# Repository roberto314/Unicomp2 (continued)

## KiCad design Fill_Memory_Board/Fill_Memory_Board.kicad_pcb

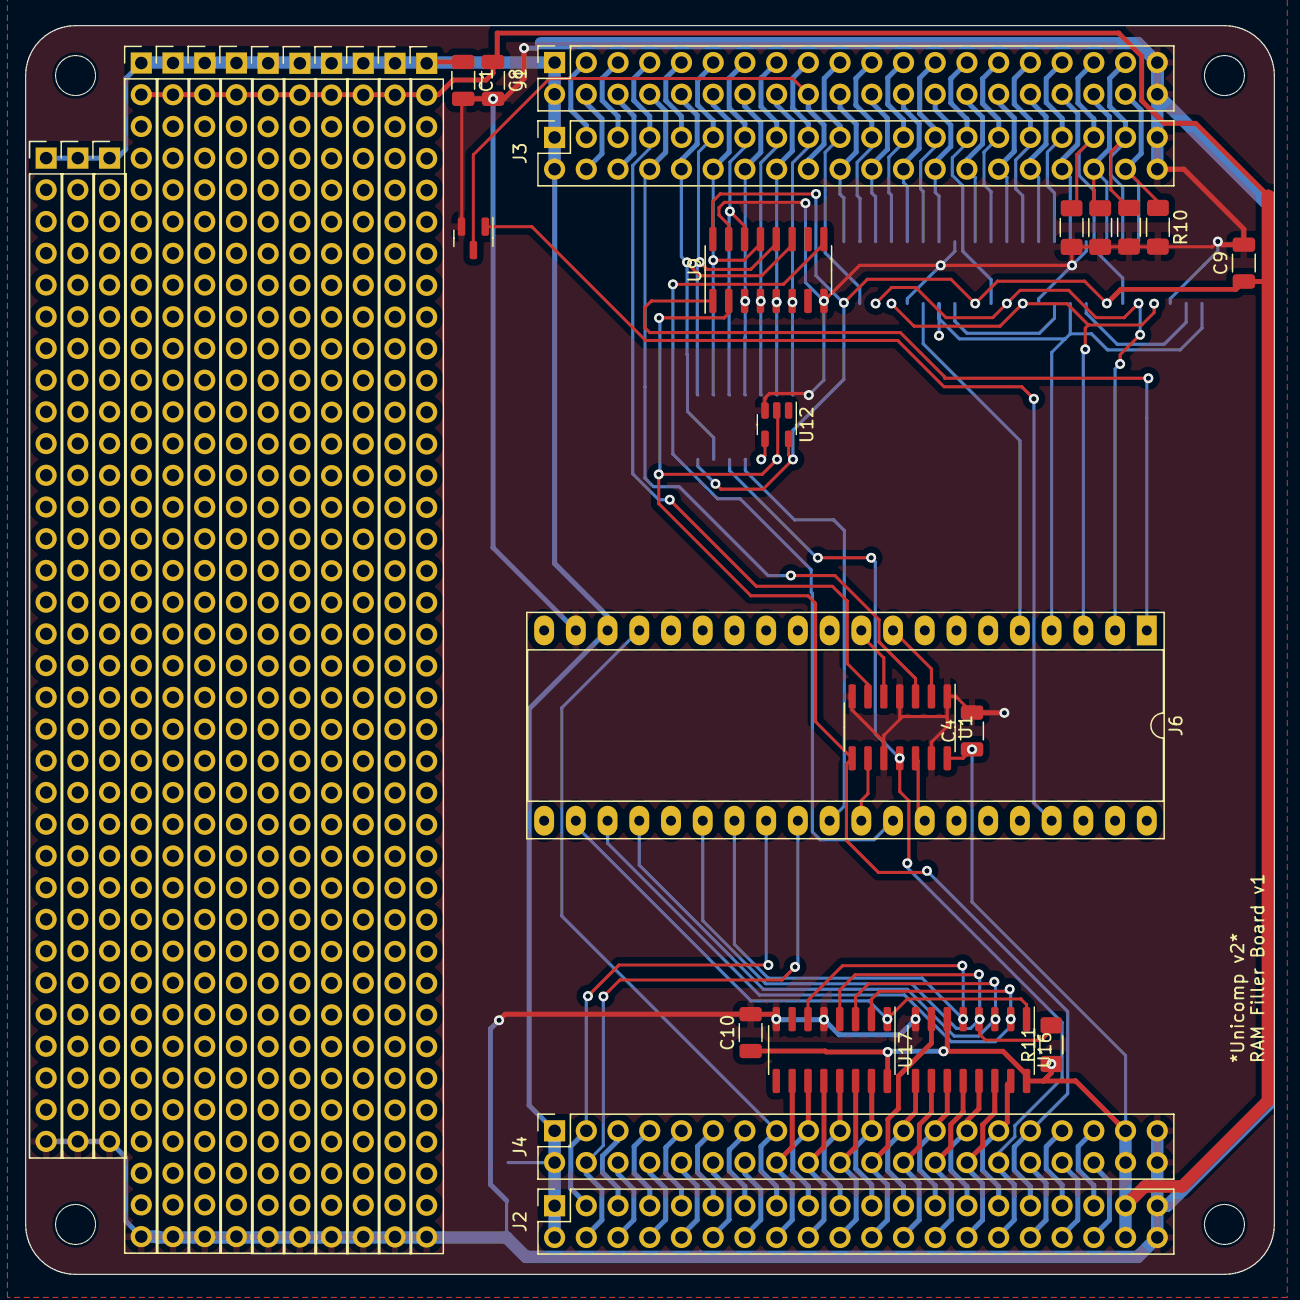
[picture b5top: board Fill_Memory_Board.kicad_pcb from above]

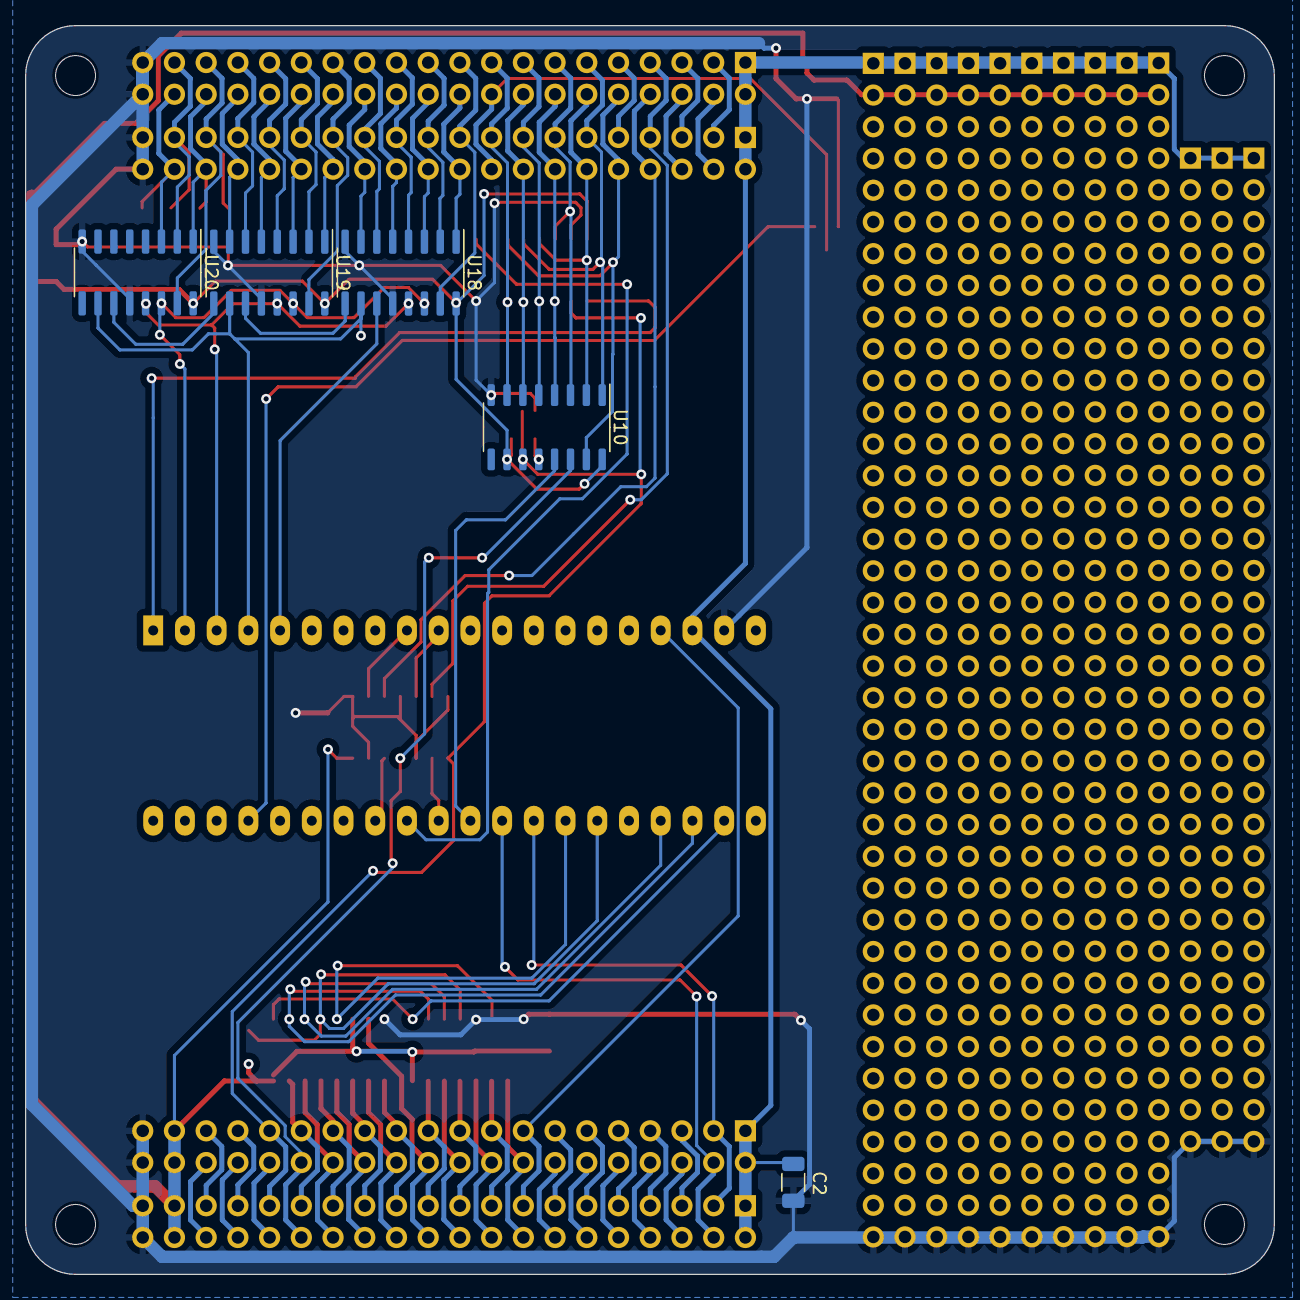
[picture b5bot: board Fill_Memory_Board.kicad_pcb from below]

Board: 2 copper layers, 100.0 x 100.0 mm, 43 parts (5 on the bottom side), 93 nets.

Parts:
C1, C2, C4, C8, C9, C10: 100n; C_1206_3216Metric
H1, H2, H3, H4: MountingHole; MountingHole_3.2mm_M3
J1, J2, J3, J4: BUS; PinSocket_2x20_P2.54mm_Vertical
J6: STM32F411; DIP-40_W15.24mm_Socket_LongPads
J20, J21, J32: Conn_01x32; PinHeader_1x32_P2.54mm_Vertical
J22, J23, J24, J25, J26, J27, J28, J29, J30, J31: Conn_01x38; PinHeader_1x38_P2.54mm_Vertical
Q1: PMV450ENEAR; SOT-23
R7, R8, R9, R10, R11: 10k; R_1206_3216Metric_Pad1.30x1.75mm_HandSolder
U1: 74LS125; SOIC-14_3.9x8.7mm_P1.27mm
U9: 74LS165; SOIC-16_3.9x9.9mm_P1.27mm
U10: 74LVC595; SO-16_3.9x9.9mm_P1.27mm
U12: 74AHC1G14; SOT-23-5
U16, U17: 74LVC138; SOIC-16_3.9x9.9mm_P1.27mm
U18, U19, U20: 74HC590; SOIC-16_3.9x9.9mm_P1.27mm

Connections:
+3V3: C4.1, C8.1, C9.1, C10.1, J2.37, J2.38, J4.37, J4.38, J22.2, J23.2, J24.2, J25.2, J26.2, J27.2, J28.2, J29.2, J30.2, J31.2, R11.1, U1.14 (VCC), U9.16 (VCC), U10.10 (~SRCLR), U10.16 (VCC), U12.5 (VCC), U16.6 (E3), U16.16 (VCC), U17.16 (VCC), U18.16 (VCC), U19.16 (VCC), U20.16 (VCC)
+5V: C1.1, C2.1, J1.1, J1.2, J2.1, J2.2, J3.1, J3.2, J4.1, J4.2, J6.18, J20.1, J21.1, J22.1, J23.1, J24.1, J25.1, J26.1, J27.1, J28.1, J29.1, J30.1, J31.1, J32.1
/A0: J1.19, J3.19, U18.15 (Q0)
/A1: J1.20, J3.20, U18.1 (Q1)
/A2: J1.21, J3.21, U18.2 (Q2)
/A3: J1.22, J3.22, U18.3 (Q3)
/A4: J1.23, J3.23, U18.4 (Q4)
/A5: J1.24, J3.24, U18.5 (Q5)
/A6: J1.25, J3.25, U18.6 (Q6)
/A7: J1.26, J3.26, U18.7 (Q7)
/A8: J1.27, J3.27, U19.15 (Q0)
/A9: J1.28, J3.28, U19.1 (Q1)
/A10: J1.29, J3.29, U19.2 (Q2)
/A11: J1.30, J3.30, U19.3 (Q3)
/A12: J1.31, J3.31, U19.4 (Q4)
/A13: J1.32, J3.32, U19.5 (Q5)
/A14: J1.33, J3.33, U19.6 (Q6)
/A15: J1.34, J3.34, U19.7 (Q7)
/A16: J1.35, J3.35, R7.1, U20.15 (Q0)
/A17: J1.36, J3.36, R8.1, U20.1 (Q1)
/A18: J1.37, J3.37, R9.1, U20.2 (Q2)
/A19: J1.38, J3.38, R10.1, U20.3 (Q3)
/B10: J6.37, Q1.1 (G)
/Bus/TDRTN: J2.32, J4.32
/CLKF: J2.14, J4.14
/CLKS: J2.13, J4.13
/CNT: J6.5, U18.11 (CPC)
/CPR: J6.3, U18.13 (CPR), U19.13 (CPR), U20.13 (CPR)
/D0: J1.10, J3.10, U9.11 (D0), U10.15 (QA)
/D1: J1.11, J3.11, U9.12 (D1), U10.1 (QB)
/D2: J1.12, J3.12, U9.13 (D2), U10.2 (QC)
/D3: J1.13, J3.13, U9.14 (D3), U10.3 (QD)
/D4: J1.14, J3.14, U9.3 (D4), U10.4 (QE)
/D5: J1.15, J3.15, U9.4 (D5), U10.5 (QF)
/D6: J1.16, J3.16, U9.5 (D6), U10.6 (QG)
/D7: J1.17, J3.17, U9.6 (D7), U10.7 (QH)
/MOSI: J2.30, J4.30, U1.11, U10.14 (SER)
/OFF/ON: J6.26, R11.2, U16.4 (E1), U17.4 (E1)
/PH0: J2.11, J4.11
/PHI1_e: J1.3, J3.3
/PHI2_e: J1.4, J3.4
/RES0: J2.7, J4.7
/RES1: J2.9, J4.9
/RX1: J2.10, J4.10
/RX2: J2.3, J4.3, J6.28
/RX3: J2.5, J4.5
/R/~W_e: J1.6, J3.6
/SCK: J2.31, J4.31, U1.8, U9.2 (CP), U10.11 (SRCLK), U12.2
/SEL0: J6.22, U16.1 (A0), U17.1 (A0)
/SEL1: J6.23, U16.2 (A1), U17.2 (A1)
/SEL2: J6.24, U16.3 (A2), U17.3 (A2)
/SEL4: J6.27, U16.5 (E2), U17.6 (E3)
/TCK: J2.35, J4.35
/TDI: J2.36, J4.36
/TDO: J2.34, J4.34
/TMS: J2.33, J4.33
/TX1: J2.8, J4.8
/TX2: J2.4, J4.4, J6.29
/TX3: J2.6, J4.6
/UMISO: J6.32, U9.9 (Q7)
/uMOSI: J6.33, U1.12
/uSCK: J6.31, U1.9
/~BUSFREE: J2.15, J4.15, J6.17
/~CNTOE: J6.2, U18.14 (~OE), U19.14 (~OE), U20.14 (~OE)
/~DATOE: J6.30, U10.13 (~OE)
/~IORD: J1.5, J3.5
/~IOWR: J1.9, J3.9
/~MRC: J6.4, U18.10 (~MRC), U19.10 (~MRC), U20.10 (~MRC)
/~MRD: J1.7, J3.7, U1.6
/~MWR: J1.8, J3.8, U1.3
/~PH0: J2.12, J4.12
/~PLD: J6.1, U9.1 (~PL)
/~RAMWE0: J2.29, J4.29, U16.15 (O0)
/~RAMWE1: J2.28, J4.28, U16.14 (O1)
/~RAMWE2: J2.27, J4.27, U16.13 (O2)
/~RAMWE3: J2.26, J4.26, U16.12 (O3)
/~RAMWE4: J2.25, J4.25, U16.11 (O4)
/~RAMWE5: J2.24, J4.24, U16.10 (O5)
/~RAMWE6: J2.23, J4.23, U16.9 (O6)
/~RAMWE7: J2.22, J4.22, U16.7 (O7)
/~RAMWE8: J2.21, J4.21, U17.15 (O0)
/~RAMWE9: J2.20, J4.20, U17.14 (O1)
/~RAMWE10: J2.19, J4.19, U17.13 (O2)
/~RAMWE11: J2.18, J4.18, U17.12 (O3)
/~RAMWE12: J2.17, J4.17, U17.11 (O4)
/~RAMWE13: J2.16, J4.16, U17.10 (O5)
/~RST: J1.18, J3.18, Q1.3 (D)
/~uMRD: J6.10, U1.5
/~uMWR: J6.9, U1.2
GND: C1.2, C2.2, C4.2, C8.2, C9.2, C10.2, J1.39, J1.40, J2.39, J2.40, J3.39, J3.40, J4.39, J4.40, J6.19, J20.32, J21.32, J22.38, J23.38, J24.38, J25.38, J26.38, J27.38, J28.38, J29.38, J30.38, J31.38, J32.32, Q1.2 (S), R7.2, R8.2, R9.2, R10.2, U1.1, U1.4, U1.7 (GND), U1.10, U1.13, U9.8 (GND), U9.15 (~CE), U10.8 (GND), U12.3 (GND), U16.8 (GND), U17.5 (E2), U17.8 (GND), U18.8 (GND), U18.12 (~CE), U19.8 (GND), U19.12 (~CE), U20.8 (GND), U20.12 (~CE)
unnamed: U10.12 (RCLK), U12.4
unnamed: U18.9 (~RCO), U19.11 (CPC)
unnamed: U19.9 (~RCO), U20.11 (CPC)

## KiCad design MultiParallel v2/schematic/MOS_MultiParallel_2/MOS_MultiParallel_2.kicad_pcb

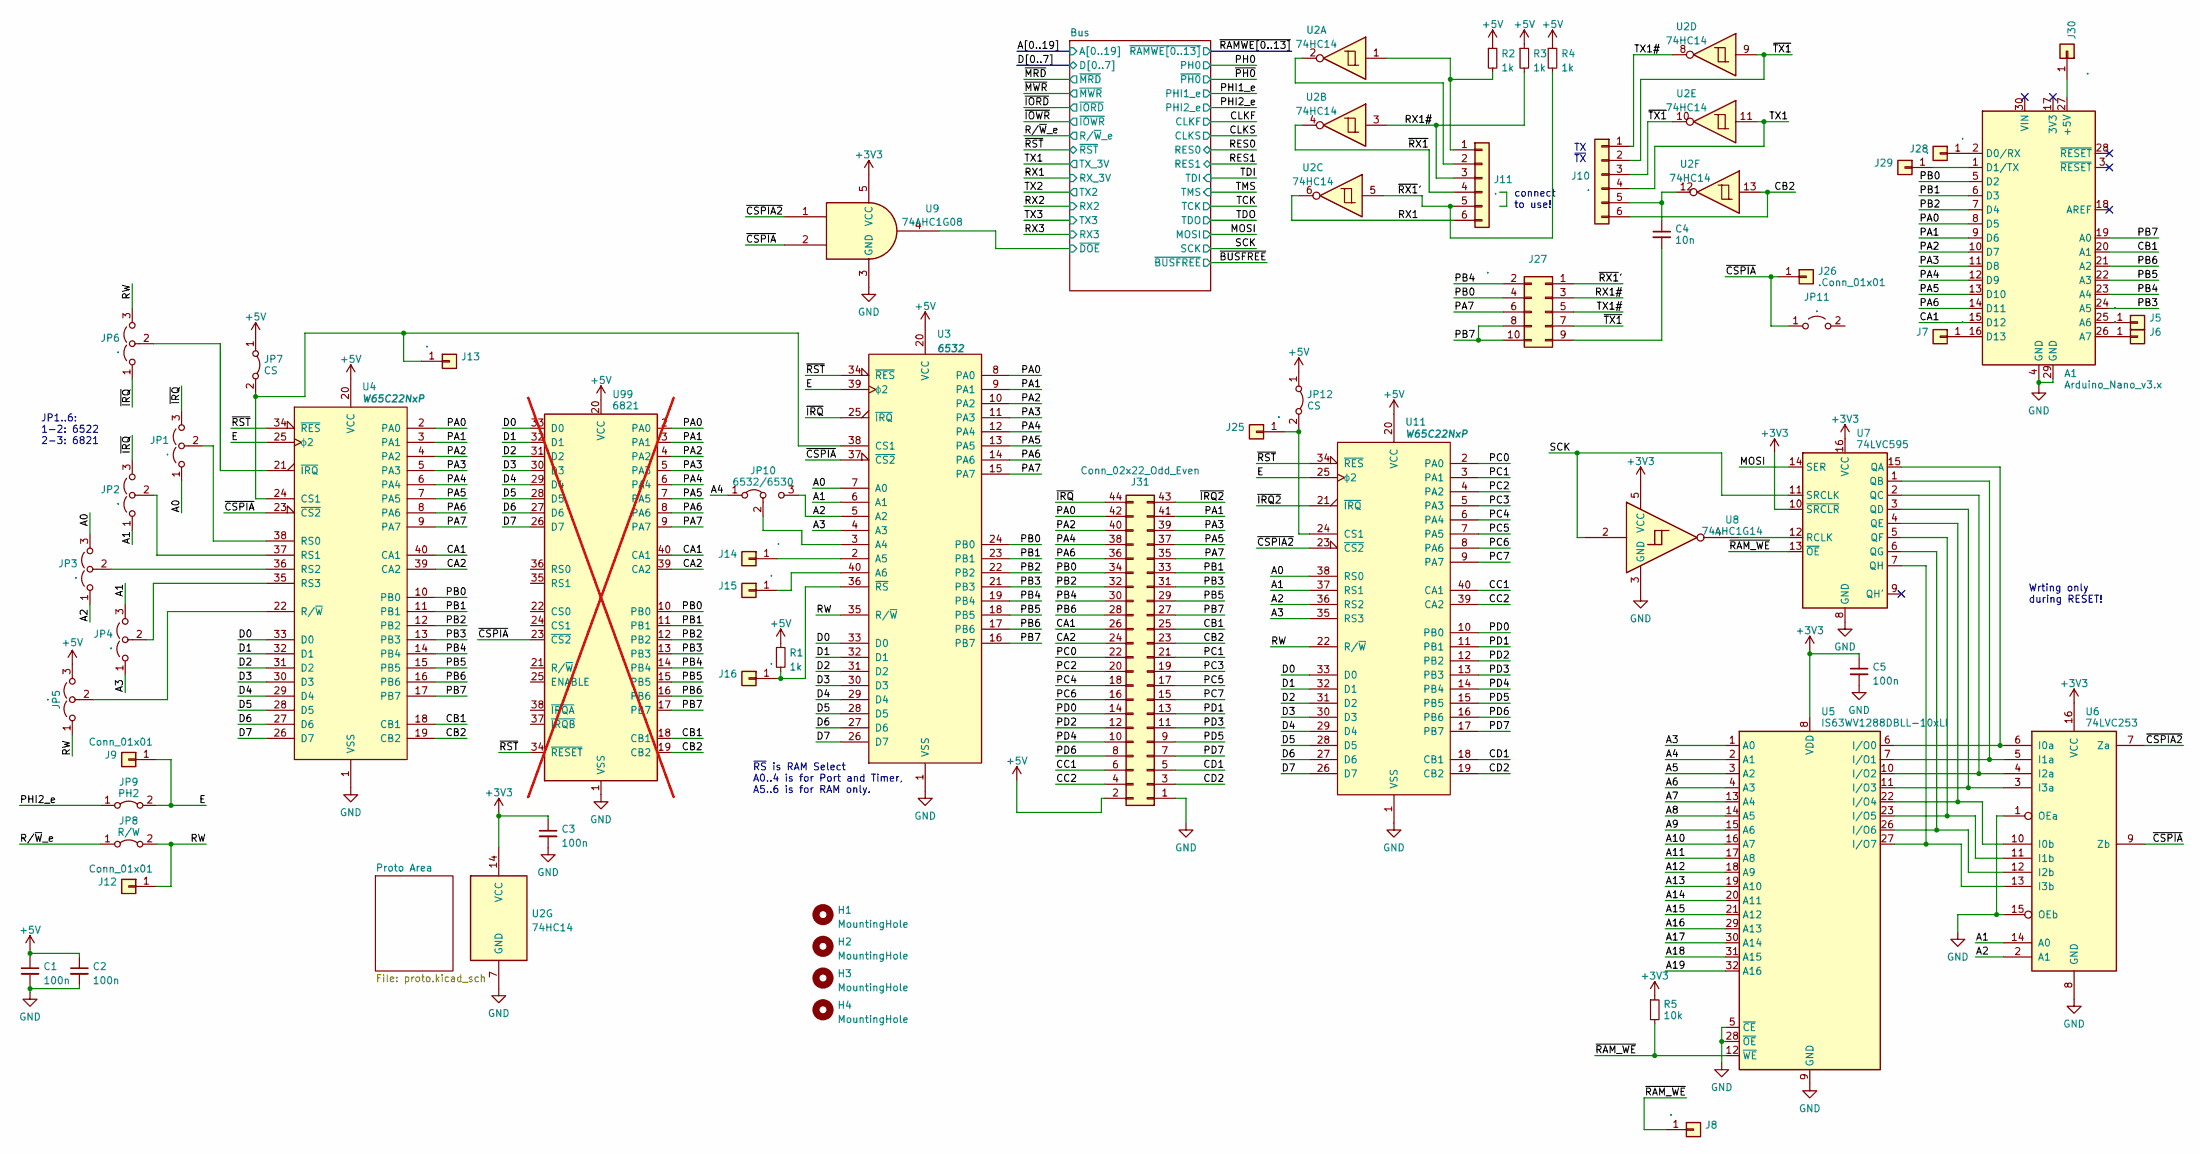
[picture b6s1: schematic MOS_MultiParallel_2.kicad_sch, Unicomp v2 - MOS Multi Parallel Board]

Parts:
A1: Arduino_Nano_v3.x; Arduino_Nano
C1, C2, C3, C5: 100n; C_1206_3216Metric
C4: 10n; C_1206_3216Metric
H1, H2, H3, H4: MountingHole; MountingHole_3.2mm_M3
J5, J6, J7, J8, J13, J14, J15, J16, J25, J28, J29, J30: .; PinHeader_1x01_P2.00mm_Vertical
J9, J12: Conn_01x01; PinHeader_1x01_P2.00mm_Vertical
J10, J11: .; PinHeader_1x06_P2.54mm_Vertical
J26: .Conn_01x01; PinHeader_1x01_P2.00mm_Vertical
J27: .; PinHeader_2x05_P2.54mm_Vertical
J31: Conn_02x22_Odd_Even; PinHeader_2x22_P2.54mm_Vertical
JP1, JP2, JP3, JP4, JP5, JP6: .; PinHeader_1x03_P2.54mm_Vertical
JP7, JP12: CS; SolderJumper-2_P1.3mm_Bridged_RoundedPad1.0x1.5mm
JP8: R/W; SolderJumper-2_P1.3mm_Bridged_RoundedPad1.0x1.5mm
JP9: PH2; SolderJumper-2_P1.3mm_Bridged_RoundedPad1.0x1.5mm
JP10: 6532/6530; SolderJumper-3_P1.3mm_Bridged12_Pad1.0x1.5mm_NumberLabels
JP11: .; SolderJumper-2_P1.3mm_Open_RoundedPad1.0x1.5mm
R1, R2, R3, R4: 1k; R_1206_3216Metric_Pad1.30x1.75mm_HandSolder
R5: 10k; R_1206_3216Metric_Pad1.30x1.75mm_HandSolder
U2: 74HC14; DIP-14_W7.62mm_Socket
U3: 6532; DIP-40_W15.24mm_Socket_LongPads
U4, U11: W65C22NxP; DIP-40_W15.24mm_Socket_LongPads
U5: IS63WV1288DBLL-10xLI; TSOP-II-32_21.0x10.2mm_P1.27mm
U6: 74LVC253; SO-16_3.9x9.9mm_P1.27mm
U7: 74LVC595; SO-16_3.9x9.9mm_P1.27mm
U8: 74AHC1G14; SOT-23-5
U9: 74AHC1G08; SOT-23-5_HandSoldering
U99: 6821; DIP-40_W15.24mm; not fitted

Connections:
+3V3: C3.1, C5.1, R5.1, U2.14 (VCC), U5.8 (VDD), U5.24 (VDD), U6.16 (VCC), U7.10 (~SRCLR), U7.16 (VCC), U8.5 (VCC), U9.5 (VCC); also elsewhere on the board
+5V: C1.1, C2.1, J31.2, JP5.3 (B), JP7.1 (A), JP12.1 (A), R1.1, R2.1, R3.1, R4.1, U3.20 (VCC), U4.20 (VCC), U11.20 (VCC), U99.20 (VCC); also elsewhere on the board
/A0: JP1.1 (A), JP3.3 (B), U3.7 (A0), U11.38 (RS0); also elsewhere on the board
/A1: JP2.1 (A), JP4.3 (B), U3.6 (A1), U6.14 (A0), U11.37 (RS1); also elsewhere on the board
/A2: JP3.1 (A), JP10.3 (B), U3.5 (A2), U6.2 (A1), U11.36 (RS2); also elsewhere on the board
/A3: JP4.1 (A), U3.4 (A3), U5.1 (A0), U11.35 (RS3); also elsewhere on the board
/A4: JP10.1 (A), U5.2 (A1); also elsewhere on the board
/A5: U5.3 (A2); also elsewhere on the board
/A6: U5.4 (A3); also elsewhere on the board
/A7: U5.13 (A4); also elsewhere on the board
/A8: U5.14 (A5); also elsewhere on the board
/A9: U5.15 (A6); also elsewhere on the board
/A10: U5.16 (A7); also elsewhere on the board
/A11: U5.17 (A8); also elsewhere on the board
/A12: U5.18 (A9); also elsewhere on the board
/A13: U5.19 (A10); also elsewhere on the board
/A14: U5.20 (A11); also elsewhere on the board
/A15: U5.21 (A12); also elsewhere on the board
/A16: U5.29 (A13); also elsewhere on the board
/A17: U5.30 (A14); also elsewhere on the board
/A18: U5.31 (A15); also elsewhere on the board
/A19: U5.32 (A16); also elsewhere on the board
/CA1: A1.15 (D12), J31.26, U4.40 (CA1), U99.40 (CA1)
/CA2: J31.24, U4.39 (CA2), U99.39 (CA2)
/CB1: A1.20 (A1), J31.25, U4.18 (CB1), U99.18 (CB1)
/CB2: J10.6, J31.23, U2.13, U4.19 (CB2), U99.19 (CB2)
/CC1: J31.6, U11.40 (CA1)
/CC2: J31.4, U11.39 (CA2)
/CD1: J31.5, U11.18 (CB1)
/CD2: J31.3, U11.19 (CB2)
/D0: U3.33 (D0), U4.33 (D0), U11.33 (D0), U99.33 (D0); also elsewhere on the board
/D1: U3.32 (D1), U4.32 (D1), U11.32 (D1), U99.32 (D1); also elsewhere on the board
/D2: U3.31 (D2), U4.31 (D2), U11.31 (D2), U99.31 (D2); also elsewhere on the board
/D3: U3.30 (D3), U4.30 (D3), U11.30 (D3), U99.30 (D3); also elsewhere on the board
/D4: U3.29 (D4), U4.29 (D4), U11.29 (D4), U99.29 (D4); also elsewhere on the board
/D5: U3.28 (D5), U4.28 (D5), U11.28 (D5), U99.28 (D5); also elsewhere on the board
/D6: U3.27 (D6), U4.27 (D6), U11.27 (D6), U99.27 (D6); also elsewhere on the board
/D7: U3.26 (D7), U4.26 (D7), U11.26 (D7), U99.26 (D7); also elsewhere on the board
/E: J9.1, JP9.2 (B), U3.39 (ϕ2), U4.25 (ϕ2), U11.25 (ϕ2)
/MOSI: U7.14 (SER); also elsewhere on the board
/PA0: A1.8 (D5), J31.42, U3.8 (PA0), U4.2 (PA0), U99.2 (PA0)
/PA1: A1.9 (D6), J31.41, U3.9 (PA1), U4.3 (PA1), U99.3 (PA1)
/PA2: A1.10 (D7), J31.40, U3.10 (PA2), U4.4 (PA2), U99.4 (PA2)
/PA3: A1.11 (D8), J31.39, U3.11 (PA3), U4.5 (PA3), U99.5 (PA3)
/PA4: A1.12 (D9), J31.38, U3.12 (PA4), U4.6 (PA4), U99.6 (PA4)
/PA5: A1.13 (D10), J31.37, U3.13 (PA5), U4.7 (PA5), U99.7 (PA5)
/PA6: A1.14 (D11), J31.36, U3.14 (PA6), U4.8 (PA6), U99.8 (PA6)
/PA7: J27.6, J31.35, U3.15 (PA7), U4.9 (PA7), U99.9 (PA7)
/PB0: A1.5 (D2), J27.4, J31.34, U3.24 (PB0), U4.10 (PB0), U99.10 (PB0)
/PB1: A1.6 (D3), J31.33, U3.23 (PB1), U4.11 (PB1), U99.11 (PB1)
/PB2: A1.7 (D4), J31.32, U3.22 (PB2), U4.12 (PB2), U99.12 (PB2)
/PB3: A1.24 (A5), J31.31, U3.21 (PB3), U4.13 (PB3), U99.13 (PB3)
/PB4: A1.23 (A4), J27.2, J31.30, U3.19 (PB4), U4.14 (PB4), U99.14 (PB4)
/PB5: A1.22 (A3), J31.29, U3.18 (PB5), U4.15 (PB5), U99.15 (PB5)
/PB6: A1.21 (A2), J31.28, U3.17 (PB6), U4.16 (PB6), U99.16 (PB6)
/PB7: A1.19 (A0), J27.8, J27.10, J31.27, U3.16 (PB7), U4.17 (PB7), U99.17 (PB7)
/PC0: J31.22, U11.2 (PA0)
/PC1: J31.21, U11.3 (PA1)
/PC2: J31.20, U11.4 (PA2)
/PC3: J31.19, U11.5 (PA3)
/PC4: J31.18, U11.6 (PA4)
/PC5: J31.17, U11.7 (PA5)
/PC6: J31.16, U11.8 (PA6)
/PC7: J31.15, U11.9 (PA7)
/PD0: J31.14, U11.10 (PB0)
/PD1: J31.13, U11.11 (PB1)
/PD2: J31.12, U11.12 (PB2)
/PD3: J31.11, U11.13 (PB3)
/PD4: J31.10, U11.14 (PB4)
/PD5: J31.9, U11.15 (PB5)
/PD6: J31.8, U11.16 (PB6)
/PD7: J31.7, U11.17 (PB7)
/PHI2_e: JP9.1 (A); also elsewhere on the board
/RX1: J11.6, U2.6; also elsewhere on the board
/RX1#: J11.3, J27.3, R3.2, U2.3
/SCK: U7.11 (SRCLK), U8.2; also elsewhere on the board
/TX1: J10.4, U2.11; also elsewhere on the board
/TX1#: J10.1, J27.5, U2.8
/~CSPIA2: U6.7 (Za), U9.1, U11.23 (~CS2)
/~CSPIA: J26.1, JP11.1 (A), U3.37 (~CS2), U4.23 (~CS2), U6.9 (Zb), U9.2, U99.23 (~CS2)
/~IRQ2: J31.43, U11.21 (~IRQ)
/~IRQ: J31.44, JP1.3 (B), JP2.3 (B), JP6.1 (A), U3.25 (~IRQ)
/~RAM_WE: J8.1, R5.2, U5.12 (~WE), U7.13 (~OE)
/~RST: U3.34 (~RES), U4.34 (~RES), U11.34 (~RES), U99.34 (~RESET); also elsewhere on the board
/~RX1: J11.4, U2.4
/~RX1': J11.5, J27.1, R4.2, U2.5
/~TX1: J10.2, J10.3, J27.7, U2.9, U2.10
GND: A1.4 (GND), A1.29 (GND), C1.2, C2.2, C3.2, C5.2, J31.1, U2.7 (GND), U3.1 (VSS), U4.1 (VSS), U5.5 (~CE), U5.9 (GND), U5.25 (GND), U5.28 (~OE), U6.1 (OEa), U6.8 (GND), U6.15 (OEb), U7.8 (GND), U8.3 (GND), U9.3 (GND), U11.1 (VSS), U99.1 (VSS); also elsewhere on the board
unnamed: A1.27 (+5V), J30.1
unnamed: A1.25 (A6), J5.1
unnamed: A1.26 (A7), J6.1
unnamed: A1.2 (D0/RX), J28.1
unnamed: A1.1 (D1/TX), J29.1
unnamed: A1.16 (D13), J7.1
unnamed: C4.1, J10.5, U2.12
unnamed: J11.1, R2.2, U2.1
unnamed: J11.2, U2.2
unnamed: J13.1, JP7.2 (B), U3.38 (CS1), U4.24 (CS1)
unnamed: J14.1, U3.2 (A5)
unnamed: J15.1, U3.40 (A6)
unnamed: J16.1, R1.2, U3.36 (~RS)
unnamed: J25.1, JP12.2 (B), U11.24 (CS1)
unnamed: C4.2, J27.9
unnamed: JP1.2 (C), U4.38 (RS0)
unnamed: JP2.2 (C), U4.37 (RS1)
unnamed: JP3.2 (C), U4.36 (RS2)
unnamed: JP4.2 (C), U4.35 (RS3)
unnamed: JP5.2 (C), U4.22 (R/~W)
unnamed: JP6.2 (C), U4.21 (~IRQ)
unnamed: JP10.2 (C), U3.3 (A4)
unnamed: U5.6 (I/O0), U6.6 (I0a), U7.15 (QA)
unnamed: U5.7 (I/O1), U6.5 (I1a), U7.1 (QB)
unnamed: U5.10 (I/O2), U6.4 (I2a), U7.2 (QC)
unnamed: U5.11 (I/O3), U6.3 (I3a), U7.3 (QD)
unnamed: U5.22 (I/O4), U6.10 (I0b), U7.4 (QE)
unnamed: U5.23 (I/O5), U6.11 (I1b), U7.5 (QF)
unnamed: U5.26 (I/O6), U6.12 (I2b), U7.6 (QG)
unnamed: U5.27 (I/O7), U6.13 (I3b), U7.7 (QH)
unnamed: U7.12 (RCLK), U8.4

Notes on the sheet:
Wrting only during RESET!
connect to use!
~{RS} is RAM Select A0..4 is for Port and Timer, A5..6 is for RAM only.
JP1..6: 1-2: 6522 2-3: 6821
TX ~{TX}

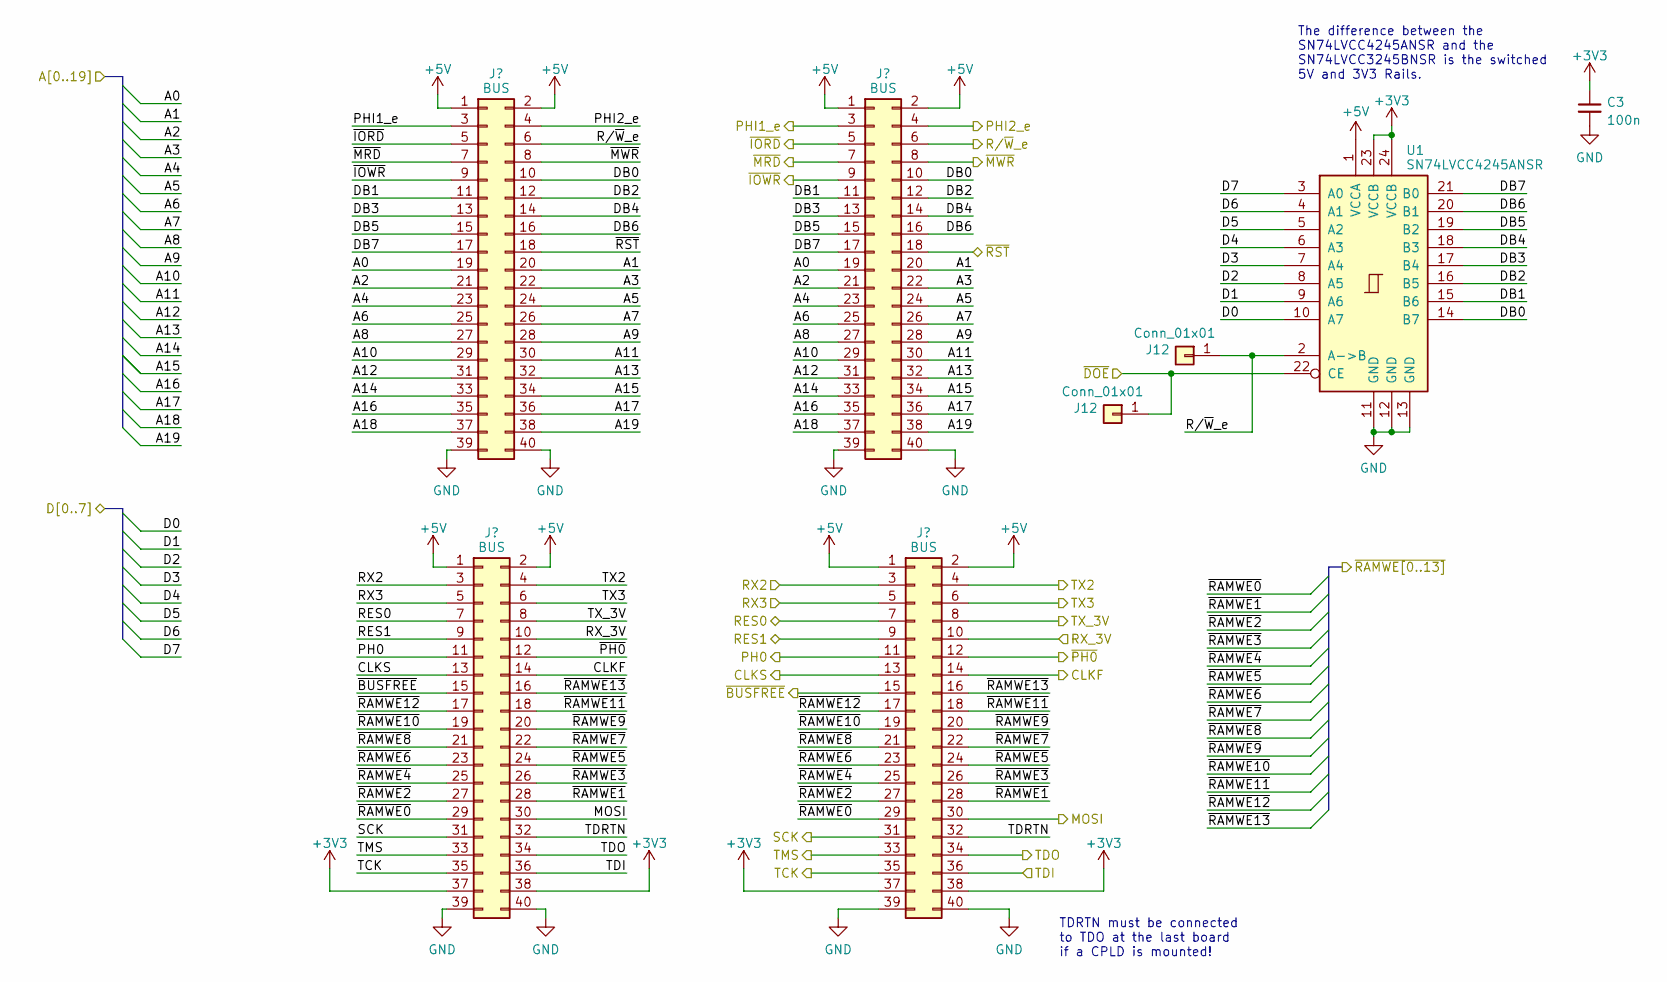
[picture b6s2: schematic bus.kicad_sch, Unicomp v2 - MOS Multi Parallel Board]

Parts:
C3: 100n; C_1206_3216Metric
J1, J2, J3, J4: BUS; PinSocket_2x20_P2.54mm_Vertical
J12: Conn_01x01; PinHeader_1x01_P2.00mm_Vertical
U1: SN74LVCC4245ANSR; SO-24_5.3x15mm_P1.27mm

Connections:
+3V3: C3.1, J2.37, J2.38, J4.37, J4.38, U1.23 (VCCB), U1.24 (VCCB); also elsewhere on the board
+5V: J1.1, J1.2, J2.1, J2.2, J3.1, J3.2, J4.1, J4.2, U1.1 (VCCA); also elsewhere on the board
/A0: J1.19, J3.19; also elsewhere on the board
/A1: J1.20, J3.20; also elsewhere on the board
/A2: J1.21, J3.21; also elsewhere on the board
/A3: J1.22, J3.22; also elsewhere on the board
/A4: J1.23, J3.23; also elsewhere on the board
/A5: J1.24, J3.24; also elsewhere on the board
/A6: J1.25, J3.25; also elsewhere on the board
/A7: J1.26, J3.26; also elsewhere on the board
/A8: J1.27, J3.27; also elsewhere on the board
/A9: J1.28, J3.28; also elsewhere on the board
/A10: J1.29, J3.29; also elsewhere on the board
/A11: J1.30, J3.30; also elsewhere on the board
/A12: J1.31, J3.31; also elsewhere on the board
/A13: J1.32, J3.32; also elsewhere on the board
/A14: J1.33, J3.33; also elsewhere on the board
/A15: J1.34, J3.34; also elsewhere on the board
/A16: J1.35, J3.35; also elsewhere on the board
/A17: J1.36, J3.36; also elsewhere on the board
/A18: J1.37, J3.37; also elsewhere on the board
/A19: J1.38, J3.38; also elsewhere on the board
/Bus/DB0: J1.10, J3.10, U1.14 (B7)
/Bus/DB1: J1.11, J3.11, U1.15 (B6)
/Bus/DB2: J1.12, J3.12, U1.16 (B5)
/Bus/DB3: J1.13, J3.13, U1.17 (B4)
/Bus/DB4: J1.14, J3.14, U1.18 (B3)
/Bus/DB5: J1.15, J3.15, U1.19 (B2)
/Bus/DB6: J1.16, J3.16, U1.20 (B1)
/Bus/DB7: J1.17, J3.17, U1.21 (B0)
/Bus/TDRTN: J2.32, J4.32
/CLKF: J2.14, J4.14
/CLKS: J2.13, J4.13
/D0: U1.10 (A7); also elsewhere on the board
/D1: U1.9 (A6); also elsewhere on the board
/D2: U1.8 (A5); also elsewhere on the board
/D3: U1.7 (A4); also elsewhere on the board
/D4: U1.6 (A3); also elsewhere on the board
/D5: U1.5 (A2); also elsewhere on the board
/D6: U1.4 (A1); also elsewhere on the board
/D7: U1.3 (A0); also elsewhere on the board
/MOSI: J2.30, J4.30; also elsewhere on the board
/PH0: J2.11, J4.11
/PHI1_e: J1.3, J3.3
/PHI2_e: J1.4, J3.4; also elsewhere on the board
/RES0: J2.7, J4.7
/RES1: J2.9, J4.9
/RX1: J2.10, J4.10; also elsewhere on the board
/RX2: J2.3, J4.3
/RX3: J2.5, J4.5
/SCK: J2.31, J4.31; also elsewhere on the board
/TCK: J2.35, J4.35
/TDI: J2.36, J4.36
/TDO: J2.34, J4.34
/TMS: J2.33, J4.33
/TX1: J2.8, J4.8; also elsewhere on the board
/TX2: J2.4, J4.4
/TX3: J2.6, J4.6
/~BUSFREE: J2.15, J4.15
/~IORD: J1.5, J3.5
/~IOWR: J1.9, J3.9
/~MRD: J1.7, J3.7
/~MWR: J1.8, J3.8
/~PH0: J2.12, J4.12
/~RAMWE0: J2.29, J4.29
/~RAMWE1: J2.28, J4.28
/~RAMWE2: J2.27, J4.27
/~RAMWE3: J2.26, J4.26
/~RAMWE4: J2.25, J4.25
/~RAMWE5: J2.24, J4.24
/~RAMWE6: J2.23, J4.23
/~RAMWE7: J2.22, J4.22
/~RAMWE8: J2.21, J4.21
/~RAMWE9: J2.20, J4.20
/~RAMWE10: J2.19, J4.19
/~RAMWE11: J2.18, J4.18
/~RAMWE12: J2.17, J4.17
/~RAMWE13: J2.16, J4.16
/~RST: J1.18, J3.18; also elsewhere on the board
GND: C3.2, J1.39, J1.40, J2.39, J2.40, J3.39, J3.40, J4.39, J4.40, U1.11 (GND), U1.12 (GND), U1.13 (GND); also elsewhere on the board

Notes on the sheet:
The difference between the SN74LVCC4245ANSR and the SN74LVCC3245BNSR is the switched 5V and 3V3 Rails.
TDRTN must be connected to TDO at the last board if a CPLD is mounted!

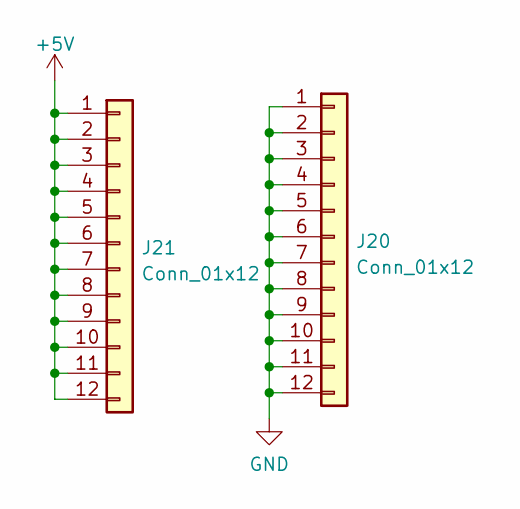
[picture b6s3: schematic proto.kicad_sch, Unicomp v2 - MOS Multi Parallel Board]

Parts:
J20, J21: Conn_01x12; PinHeader_1x12_P2.54mm_Vertical

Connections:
+5V: J21.1, J21.2, J21.3, J21.4, J21.5, J21.6, J21.7, J21.8, J21.9, J21.10, J21.11, J21.12; also elsewhere on the board
GND: J20.1, J20.2, J20.3, J20.4, J20.5, J20.6, J20.7, J20.8, J20.9, J20.10, J20.11, J20.12; also elsewhere on the board

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
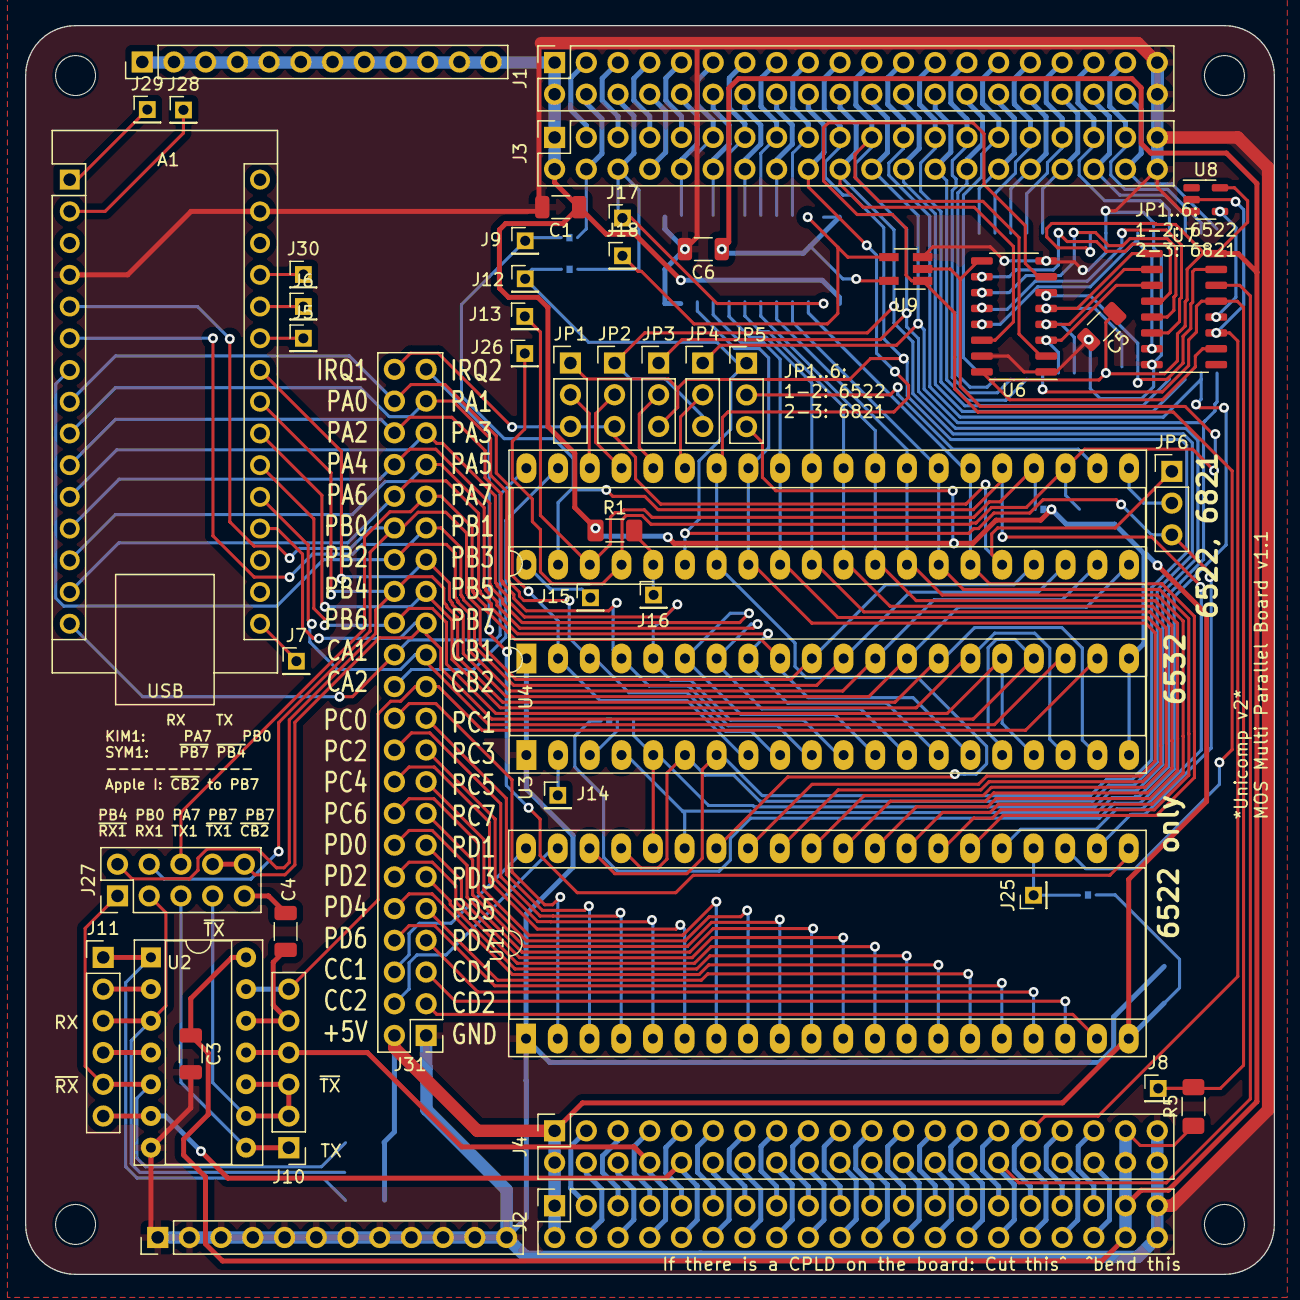
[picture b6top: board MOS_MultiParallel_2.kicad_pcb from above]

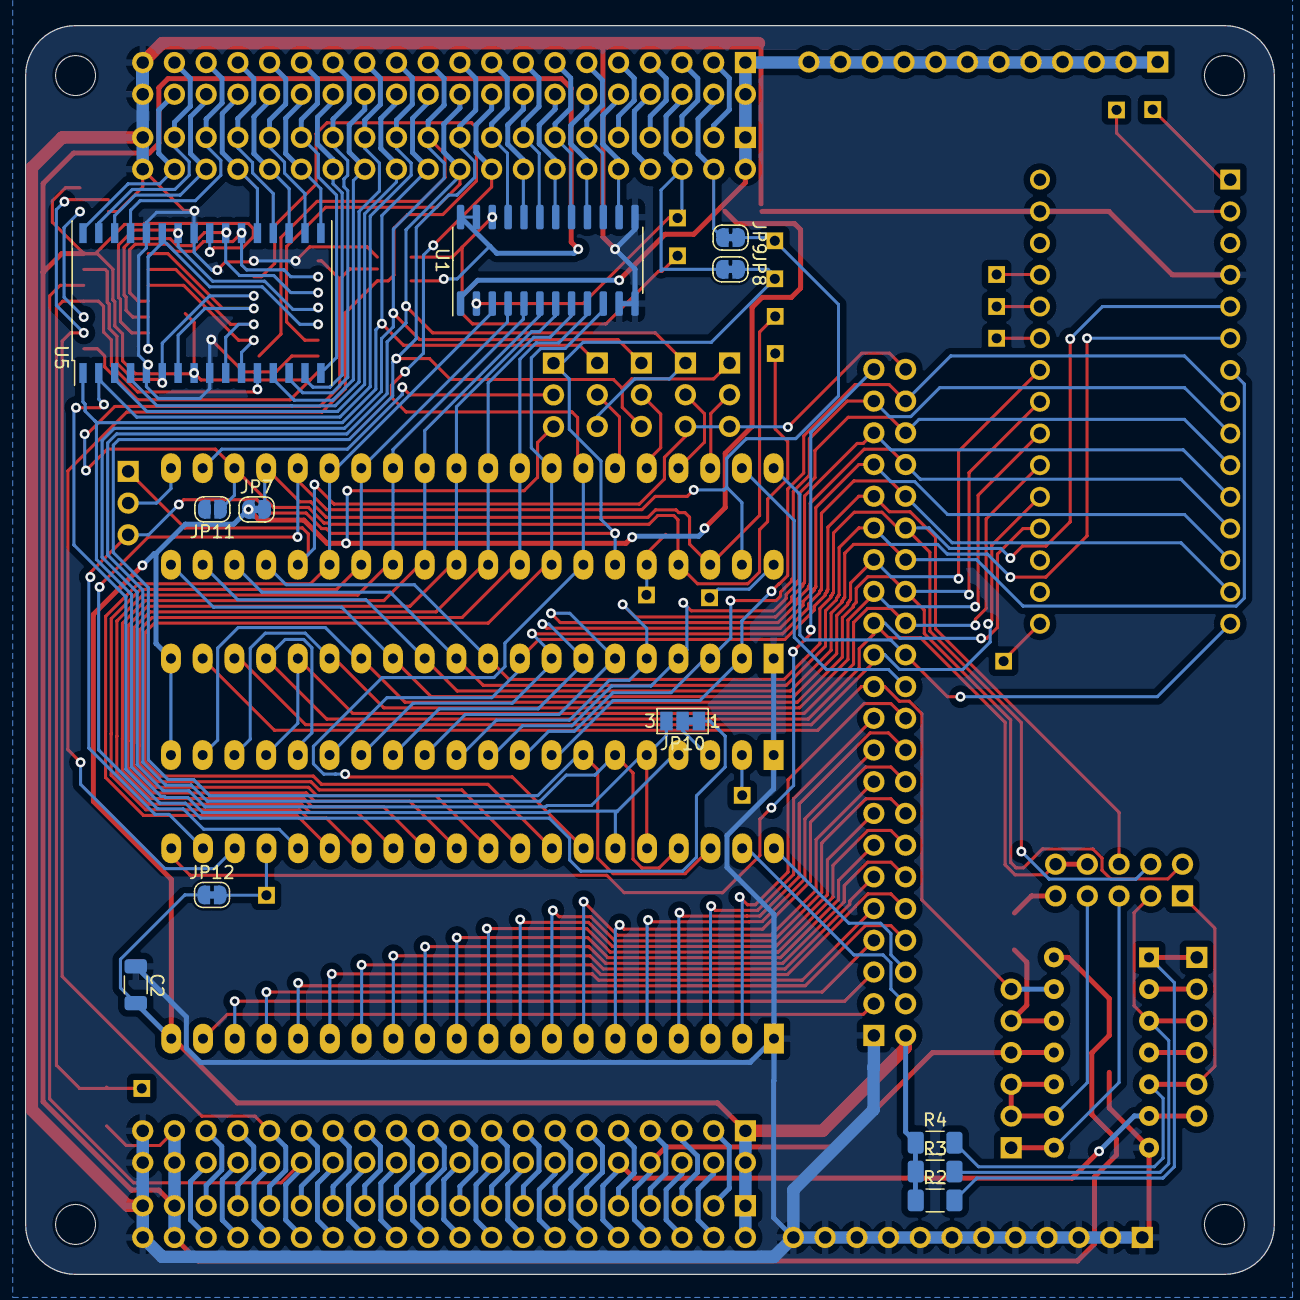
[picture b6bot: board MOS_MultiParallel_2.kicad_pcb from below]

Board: 2 copper layers, 100.0 x 100.0 mm, 65 parts (12 on the bottom side), 165 nets.

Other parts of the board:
C6: 100n; C_1206_3216Metric
J17, J18: Conn_01x01; PinHeader_1x01_P2.00mm_Vertical

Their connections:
+3V3: C6.1; also elsewhere on the board
GND: C6.2; also elsewhere on the board
